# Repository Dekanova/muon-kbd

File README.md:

# A smol and simple osu keypad

This is the Muon PCB.

## Details
Firmware for this board can be found here https://github.com/Dekanova/muon-firmware.
ROM flash is pretty big and should be able to fit whatever you want on it.

Feel free to make a PR if you get other firmware working on this board!

### Features

- RP2040 (easy firmware changes)
- hybrid MX/low profile choc hotswap socket
- rgb keyglow & underglow
- usb-c

## Usage
TODO: once hybrid keyswitch gen is merged, move from local reference

- Kicad 6.0
- openinput library from kicad content&lib manager

## Images (last updated: v0.6)

A huge thanks to openinput for their generic [KiCad lib](https://github.com/openinput-fw/openinput-kicad-library).

Also thanks to [marbastlib](https://github.com/ebastler/marbastlib) for their component lib.

This project is licenced under [CERN Open Hardware Licence v2 - Strongly Reciprocal](LICENCE) see [usage guide](LICENCE_USER_GUIDE) for more info

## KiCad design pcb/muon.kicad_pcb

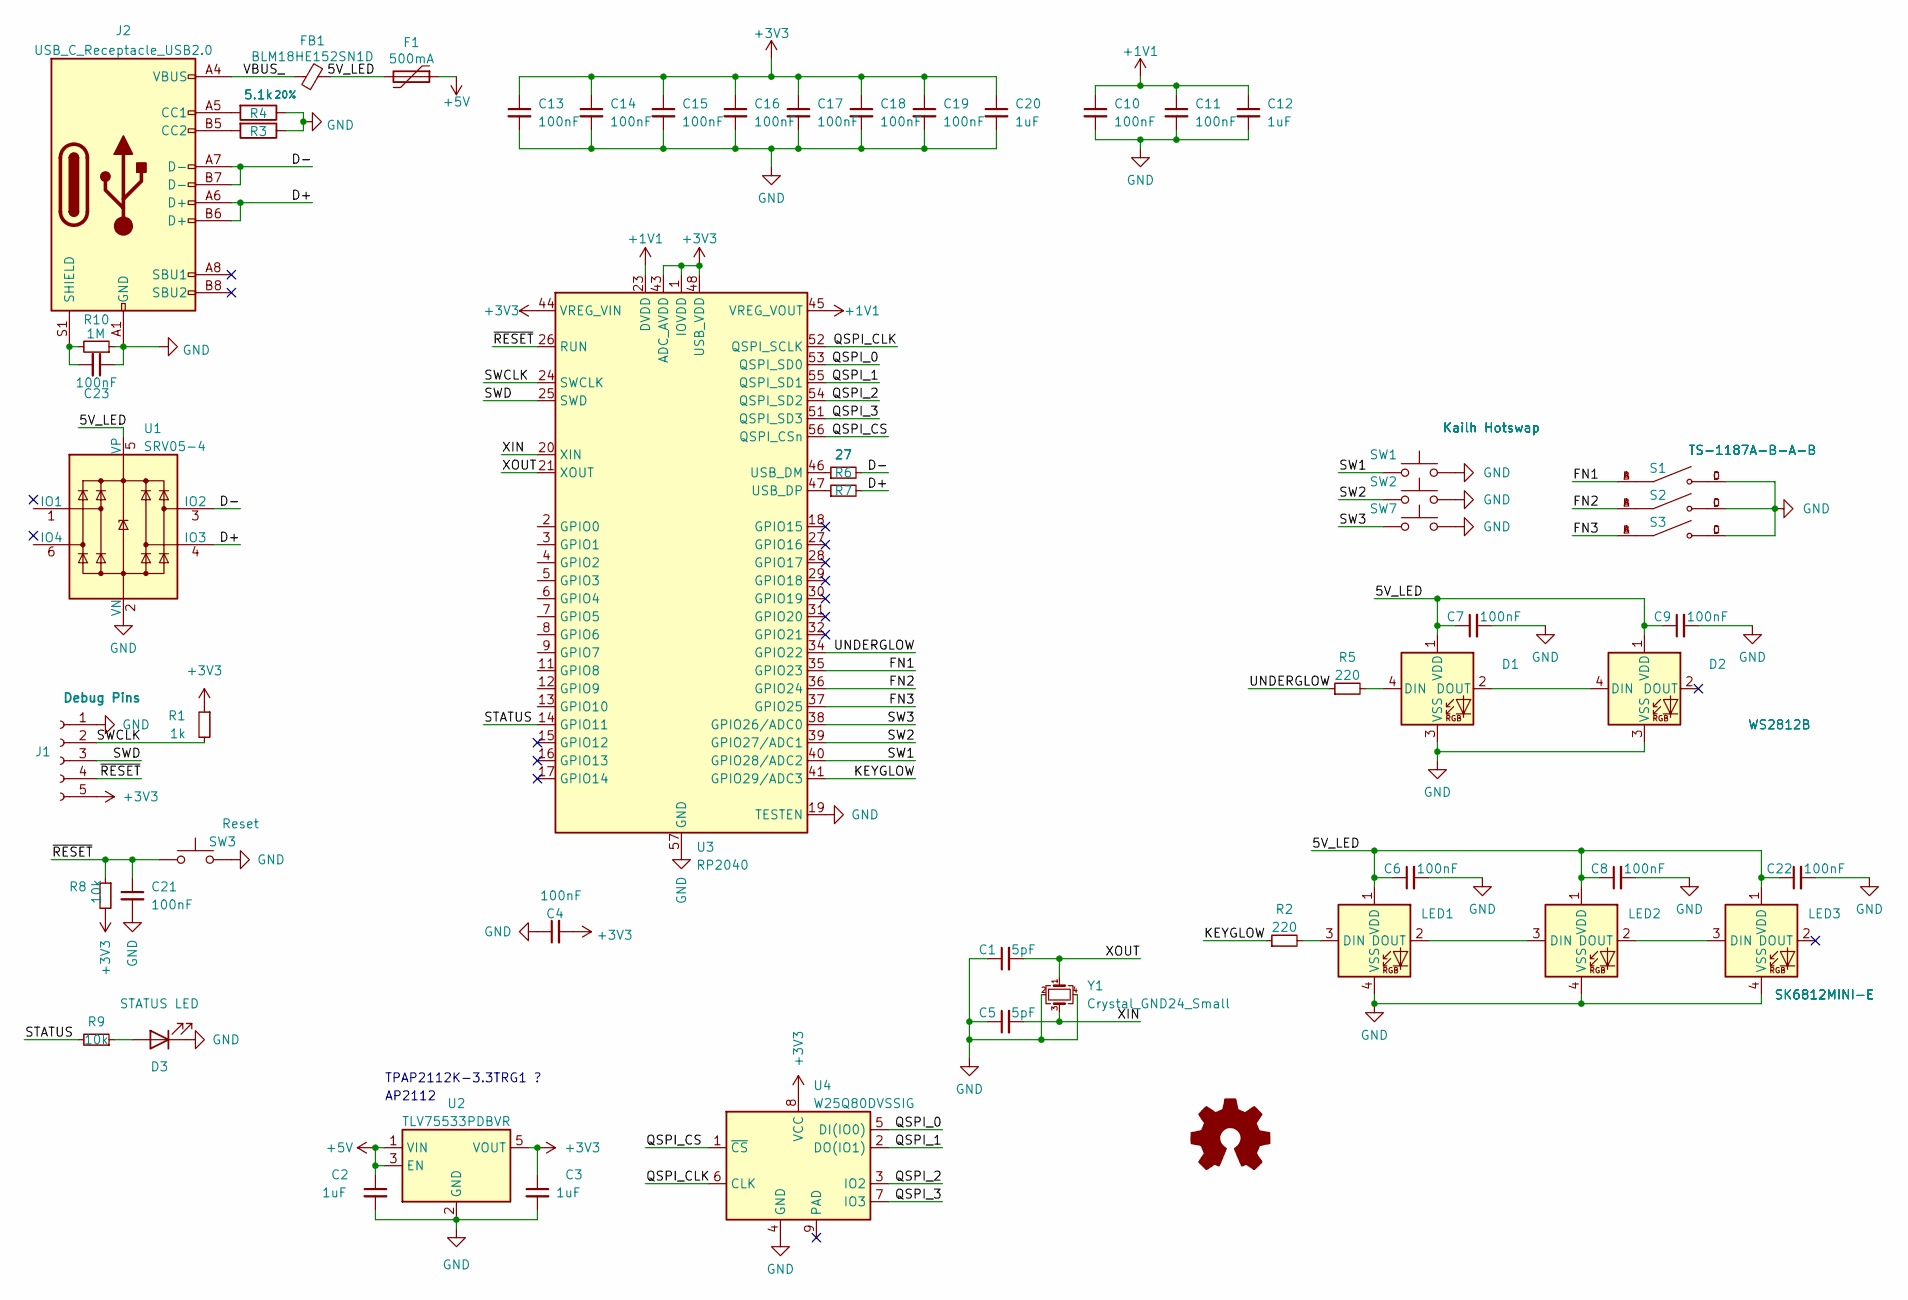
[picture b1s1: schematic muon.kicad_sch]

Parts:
C1, C5: 5pF; C_0402_1005Metric
C2, C3, C12, C20: 1uF; C_0402_1005Metric
C4, C6, C7, C8, C9, C10, C11, C13, C14, C15, C16, C17, C18, C19, C21, C22, C23: 100nF; C_0402_1005Metric
D1, D2: WS2812B; LED_WS2812B_PLCC4_5.0x5.0mm_P3.2mm
D3: STATUS LED; LED_0402_1005Metric
F1: 500mA; Fuse_0402_1005Metric
FB1: BLM18HE152SN1D; L_0603_1608Metric
J1: Debug Pins; Tag-Connect_TC2030-IDC-NL_2x03_P1.27mm_Vertical
J2: USB_C_Receptacle_USB2.0; USB_C_Receptacle_HRO_TYPE-C-31-M-12
LED1, LED2, LED3: SK6812MINI-E; LED_6028R
R1: 1k; R_0402_1005Metric
R2, R5: 220; R_0402_1005Metric
R3, R4: 5.1k; R_0402_1005Metric; Tolerance 20%
R6, R7: 27; R_0402_1005Metric
R8, R9: 10k; R_0402_1005Metric
R10: 1M; R_0402_1005Metric
S1, S2, S3: TS-1187A-B-A-B; SW_TS-1187A-B-A-B; PARTREV A0
SW1, SW2, SW7: Kailh Hotswap; SW_Hotswap_Hybrid_1.00u
SW3: Reset; SW_SPST_PTS810
U1: SRV05-4; SOT-23-6-routable
U2: TLV75533PDBVR; SOT-23-5
U3: RP2040; QFN-56-1EP_7x7mm_P0.4mm_EP3.2x3.2mm
U4: W25Q80DVSSIG; W25Q_SOIC-8
Y1: Crystal_GND24_Small; Crystal_SMD_3225-4Pin_3.2x2.5mm

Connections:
+1V1: C10.1, C11.1, C12.1, U3.23 (DVDD), U3.45 (VREG_VOUT), U3.50 (DVDD)
+3V3: C3.1, C4.2, C13.1, C14.1, C15.1, C16.1, C17.1, C18.1, C19.1, C20.1, J1.5, R1.1, R8.2, U2.5 (VOUT), U3.1 (IOVDD), U3.10 (IOVDD), U3.22 (IOVDD), U3.33 (IOVDD), U3.42 (IOVDD), U3.43 (ADC_AVDD), U3.44 (VREG_VIN), U3.48 (USB_VDD), U3.49 (IOVDD), U4.8 (VCC)
+5V: C2.1, F1.1, U2.1 (VIN), U2.3 (EN)
/5V_LED: C6.1, C7.1, C8.1, C9.1, C22.1, D1.1 (VDD), D2.1 (VDD), F1.2, FB1.2, LED1.1 (VDD), LED2.1 (VDD), LED3.1 (VDD), U1.5 (VP)
/D+: J2.A6 (D+), J2.B6 (D+), R7.2, U1.4 (IO3)
/D-: J2.A7 (D-), J2.B7 (D-), R6.2, U1.3 (IO2)
/FN1: S1.A, S1.B, U3.35 (GPIO23)
/FN2: S2.A, S2.B, U3.36 (GPIO24)
/FN3: S3.A, S3.B, U3.37 (GPIO25)
/KEYGLOW: R2.1, U3.41 (GPIO29/ADC3)
/QSPI_0: U3.53 (QSPI_SD0), U4.5 (DI(IO0))
/QSPI_1: U3.55 (QSPI_SD1), U4.2 (DO(IO1))
/QSPI_2: U3.54 (QSPI_SD2), U4.3 (IO2)
/QSPI_3: U3.51 (QSPI_SD3), U4.7 (IO3)
/QSPI_CLK: U3.52 (QSPI_SCLK), U4.6 (CLK)
/QSPI_CS: U3.56 (QSPI_CSn), U4.1 (~CS)
/STATUS: R9.2, U3.14 (GPIO11)
/SW1: SW1.1, U3.40 (GPIO28/ADC2)
/SW2: SW2.1, U3.39 (GPIO27/ADC1)
/SW3: SW7.1, U3.38 (GPIO26/ADC0)
/SWCLK: J1.2, R1.2, U3.24 (SWCLK)
/SWD: J1.3, U3.25 (SWD)
/UNDERGLOW: R5.1, U3.34 (GPIO22)
/VBUS_: FB1.1, J2.A4 (VBUS), J2.A9 (VBUS), J2.B4 (VBUS), J2.B9 (VBUS)
/XIN: C5.2, U3.20 (XIN), Y1.3
/XOUT: C1.2, U3.21 (XOUT), Y1.1
/~RESET: C21.1, J1.4, R8.1, SW3.1, U3.26 (RUN)
GND: C1.1, C2.2, C3.2, C4.1, C5.1, C6.2, C7.2, C8.2, C9.2, C10.2, C11.2, C12.2, C13.2, C14.2, C15.2, C16.2, C17.2, C18.2, C19.2, C20.2, C21.2, C22.2, C23.1, D1.3 (VSS), D2.3 (VSS), D3.1 (K), J1.1, J2.A1 (GND), J2.A12 (GND), J2.B1 (GND), J2.B12 (GND), LED1.4 (VSS), LED2.4 (VSS), LED3.4 (VSS), R3.1, R4.1, R10.1, S1.C, S1.D, S2.C, S2.D, S3.C, S3.D, SW1.2, SW2.2, SW3.2, SW7.2, U1.2 (VN), U2.2 (GND), U3.19 (TESTEN), U3.57 (GND), U4.4 (GND), Y1.2, Y1.4
unnamed: C23.2, J2.S1 (SHIELD), R10.2
unnamed: D1.2 (DOUT), D2.4 (DIN)
unnamed: D1.4 (DIN), R5.2
unnamed: D3.2 (A), R9.1
unnamed: J2.A5 (CC1), R4.2
unnamed: J2.B5 (CC2), R3.2
unnamed: LED1.2 (DOUT), LED2.3 (DIN)
unnamed: LED1.3 (DIN), R2.2
unnamed: LED2.2 (DOUT), LED3.3 (DIN)
unnamed: R6.1, U3.46 (USB_DM)
unnamed: R7.1, U3.47 (USB_DP)

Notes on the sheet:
AP2112
TPAP2112K-3.3TRG1 ?

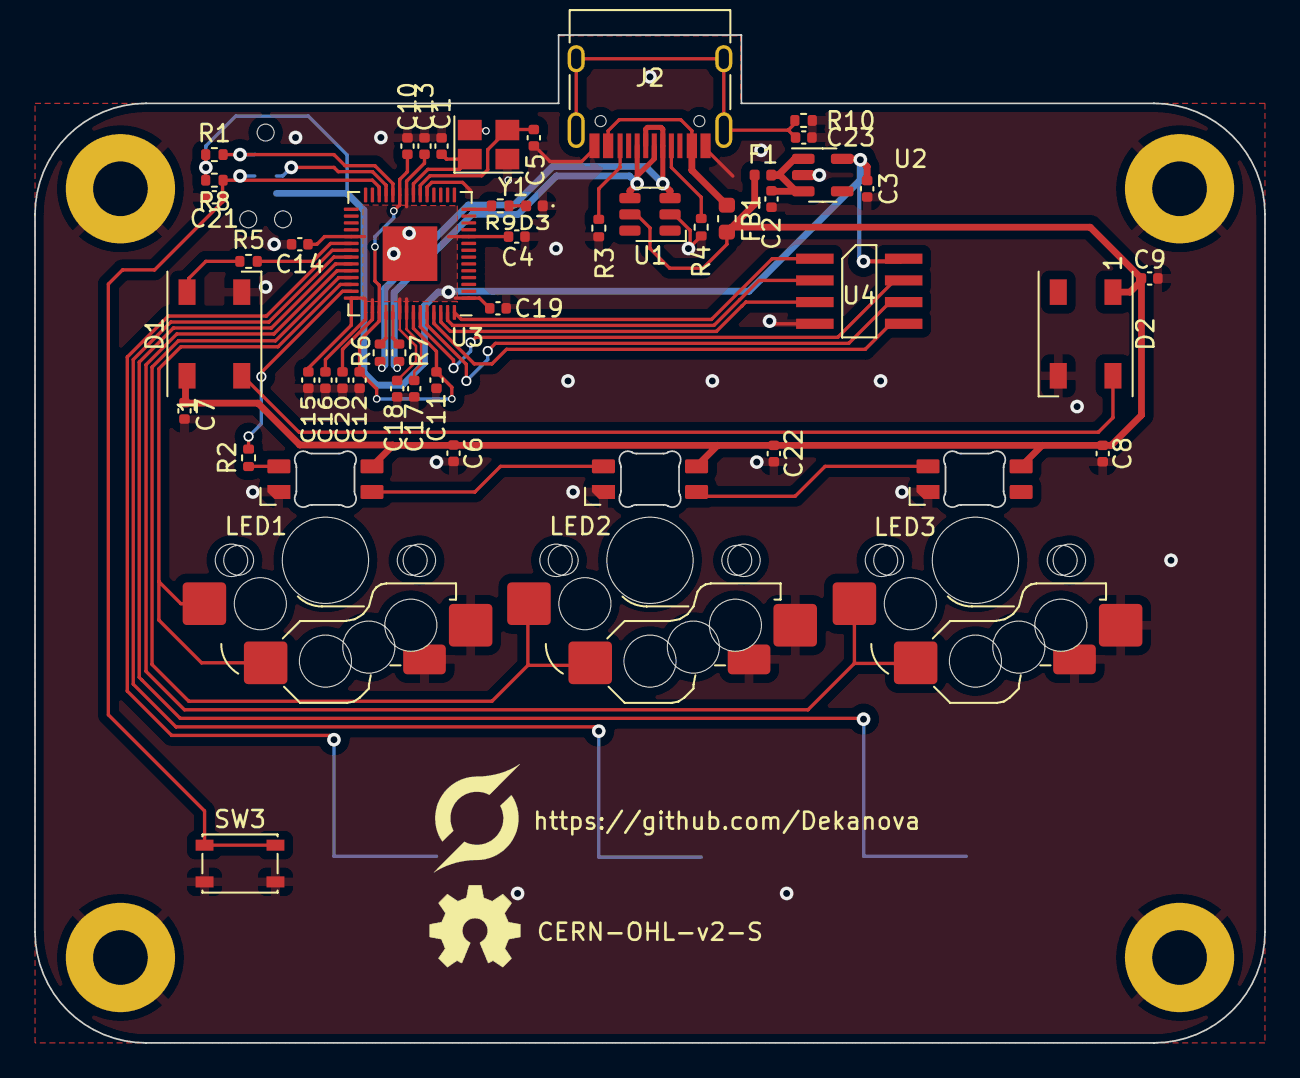
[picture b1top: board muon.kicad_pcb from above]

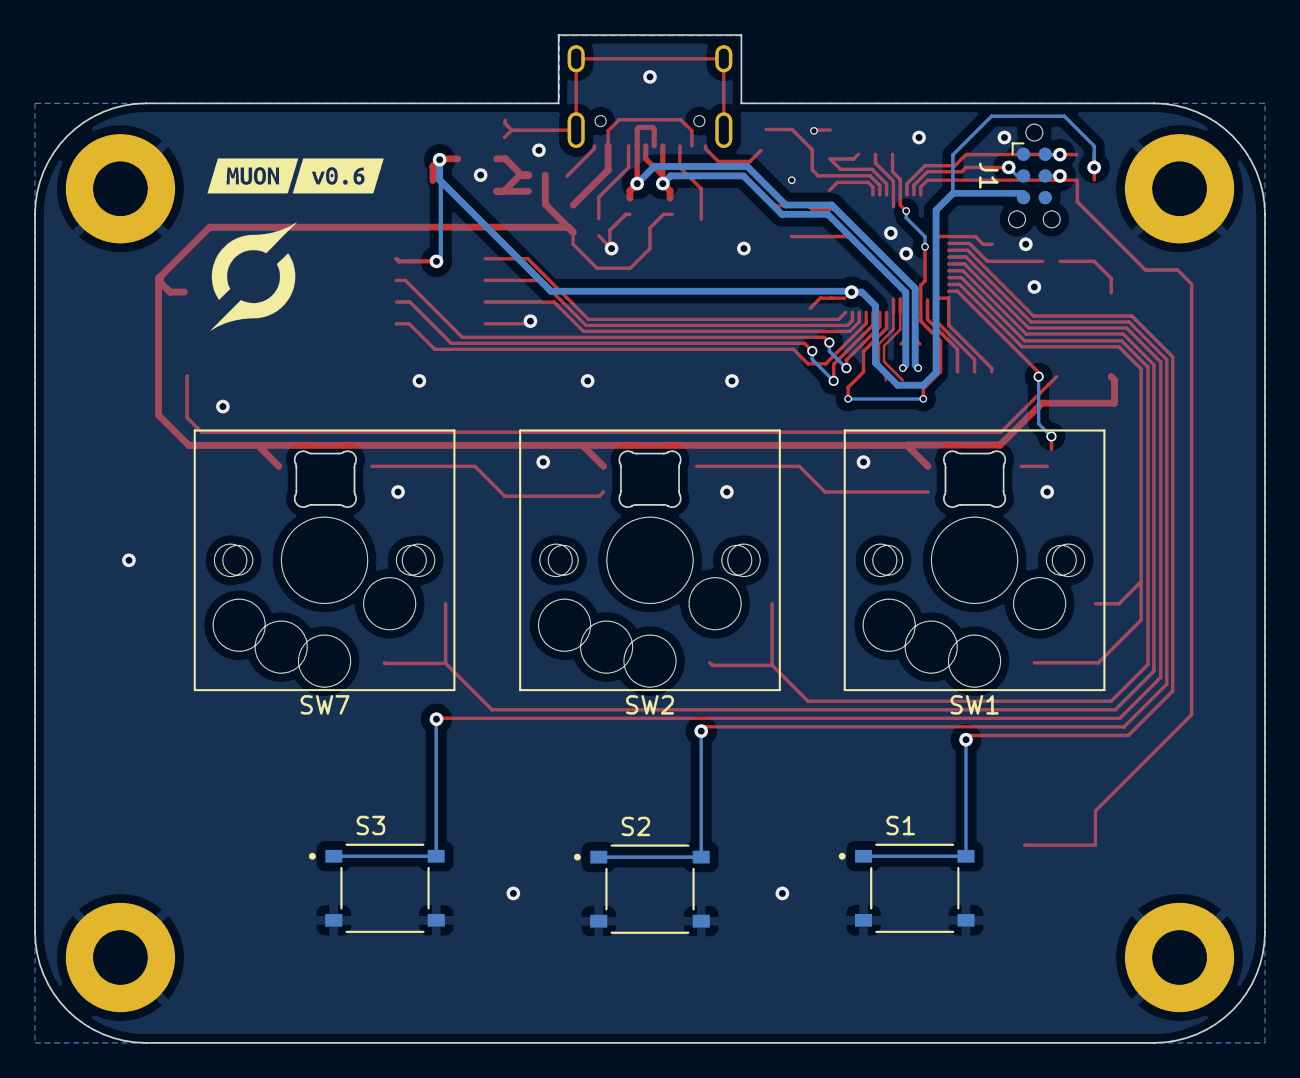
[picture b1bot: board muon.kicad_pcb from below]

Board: 2 copper layers, 72.0 x 59.0 mm, 57 parts (9 on the bottom side), 39 nets.

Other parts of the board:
kibuzzard-63718431: G***; kibuzzard-63718431
kibuzzard-63718440: G***; kibuzzard-63718440

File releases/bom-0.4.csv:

Id,Designator,Package,Quantity,Designation,Supplier and ref
1,R10,R_0402_1005Metric,1,1MΩ,
2,"C23,C16,C17,C14,C13,C18,C21,C6,C11,C4,C15,C7,C10,C19,C8,C9,C22",C_0402_1005Metric,17,100nF,
3,F1,Fuse_0402_1005Metric,1,500mA,
4,"R3,R4",R_0402_1005Metric,2,5.1k,
5,"C1,C5",C_0402_1005Metric,2,5pF,
6,"LED2,LED1,LED3",LED_6028R,3,SK6812MINI-E,
7,"R7,R6",R_0402_1005Metric,2,27Ω,
8,"D2,D1",LED_WS2812B_PLCC4_5.0x5.0mm_P3.2mm,2,WS2812B,
9,J2,USB_C_Receptacle_HRO_TYPE-C-31-M-12,1,USB_C_Receptacle_USB2.0,
10,D3,LED_0402_1005Metric,1,STATUS LED,
11,U2,SOT-23-5,1,TLV75533PDBVR,
12,"C12,C2,C20,C3",C_0402_1005Metric,4,1uF,
13,U4,W25Q_SOIC-8,1,W25Q80DVSSIG ,
14,"R9,R8",R_0402_1005Metric,2,10k,
15,SW3,SW_SPST_PTS810,1,Reset,
16,FB1,L_0402_1005Metric,1,~,
17,R1,R_0402_1005Metric,1,1k,
18,J1,PinHeader_1x05_P2.00mm_Vertical,1,Debug Pins,
19,Y1,Crystal_SMD_3225-4Pin_3.2x2.5mm,1,Crystal_GND24_Small,
20,"R2,R5",R_0402_1005Metric,2,220Ω,
21,U3,QFN-56-1EP_7x7mm_P0.4mm_EP3.2x3.2mm,1,RP2040,
22,U1,SOT-23-6-routable,1,SRV05-4,
23,"SW2,SW7,SW1",SW_Hotswap_Kailh_MX_1.00u,3,Kailh Hotswap,
24,"SW6,SW4,SW5",SW_Push_1P1T_NO_6x6mm_H9.5mm,3,DTSM-66R-V-T/R,

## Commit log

2022-02-10 add the rest of the basic components
2022-02-10 re-route traces for pretty
2022-02-11 re-route again
2022-02-21 update schematic with proper parts
2022-03-13 re-route and remove 'uneeded' things
2022-03-29 post v0.1 quick fixes
2022-05-30 add new PCB footprint lib
2022-05-31 lots of things
2022-05-31 close, but not quite v0.2
2022-06-08 add extra components for debugging and fix arragement of caps
2022-06-08 v0-2 'release' but not that release-ish
2022-06-26 minor fixes and shuffle
2022-07-01 all but 3 traces connected
2022-07-24 pre v0.3
2022-08-13 v0.3
2022-08-20 remove wireless, change LDO to more avaliable one, decouple USB shield
2022-09-02 revised v0.4, hybrid hotswap socket, fix off-center switches (off by .5mm)
2022-09-02 update readme & photos
2022-10-15 Change USB port to be on opposite side
2022-10-15 Move USB closer to the edge of the case Add gitignore
2022-10-15 Change buttons and move them into place Update 3D models
2022-10-16 broad strokes
2022-10-17 usb back on main side
2022-10-23 final touches & export fab files
2022-10-24 release v0.5
2022-11-14 Pre-v0.6 - use TagConnect debug header - equally space underglow LEDs - add comment to replicate kibuzzard settings - use M3 mounting holes
2022-11-14 update page titles, use an actual Ferrite Bead (has just been a 0ohm resistor till now
2023-02-19 update pics
2023-02-19 0.6 updates

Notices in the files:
pcb/muon.kicad_pcb:
CERN OHL v2 S
